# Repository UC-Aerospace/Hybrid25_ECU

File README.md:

# Hybrid Engine Control Unit

This repo contains the hardware and firmware for the 2025 Hybrid Rocket Engine FYP test stand electronics.

The hardware consists of three seperate modules, the central ECU alongside a servo and ADC peripheral. Central to peripheral
communication uses CAN-FD and is designed to be modular, while communications to a remote interface unit is done over RS422.
For more information on the RIU it can be found [here](https://github.com/UC-Aerospace/Hybrid25_RIU).

## Hardware

First thing to note, make sure you read the [issue!](https://github.com/UC-Aerospace/Hybrid25_ECU/issues/1).

There are issues with these designs, keep them in mind for any future development.

### MCU

The hardware of all these boards has been based on the STM32G0 MCU as a platform. The selection process for this was pretty
much based on wanting to use a STM32 for experience and the G0 in particular has two CAN-FD modems and was quite affordable.
This was a mistake, although it ended up working out okay. The STM32G0 critically lacks a SDIO peripheral which is a much
faster and more robust way of interacting with a SD card than SPI, as well as lacking QSPI and only having one SPI bus,
which meant we couldn't implement external flash memory for logging to. Given the issues with SD cards on an actual launch
vechicle that has been experienced I would have the following reccomendations:

* If you make new hardware switch MCU. Still use a ST product but pivot to something with SDIO and QSPI. Look into the F4, F7, H4 and H7 lines.
* Then implement a system where logging happens to flash during a test/launch, and then copies to SD afterwards. This means transfer to a PC
is still easy, you still get the bulk storage of SD but don't rely on it during high vibration periods.
* Don't go for a dual core. The cost increase dosn't justify the advantage and the complexity is significant.
* On cost the total sum of all the electronics this year was large enough not to worry about penny pinching on the MCU you buy maybe 5 of. $8 to $15
is inconsequential and well worth it if it saves you time.

Otherwise though the G0 has served it's purpose well this year. Honestly I have no idea how close we are cutting it with processing time overhead,
the MCU is plenty fast but a lot of the external I/O is quite slow (comms, sensors, SD card). Buffering is the name of the game in cases like that,
and trying to pass as much off to hardware peripherals as possible. Future teams could investigate a switch back to FreeRTOS for more flexibility around
scheduling, this will save some headaches and add a bunch more.

### Layout

Theres a bit of an explaination for the actual hardware design ethos to get you started in the Central ECU board directory. Otherwise between the
boards the main thing to talk about is connectors, comms and power.

The connectors we used on the peripheral boards were a compromise. JST's should never really be used where they might see forces on the wires,
but they are also cheap and the budget was getting out of hand. We mitigated this when testing by externally strain relieving all wires connecting
to both peripheral boards. Also when thinking about connectors try to keep in mind that if something can be plugged into the wrong place, it will
be plugged into the wrong place. Try to keep connectors dissimilar where you can, at least where damage would occur if they went the other way.

Comms is over CAN-FD for the peripheral to central communication and RS422 for central to RIU communication. The descision for this came because
CAN sounded cool to play with and RS422 seemed like the easiest way to get comms upto a couple hundred meters away. Both of these descisions played
out pretty well, with software headaches for both but nothing too serious. The CAN just uses premade serial DB9 cables, as these are cheap and easy
to get hold of. DB9 connectors are really solid and lock well, plus are rated to about 3A per pin. For the link to the RIU we just used generic CAT5
cable, two of the pairs are used for RS422 with another used for the ESTOP signal lines. The plastic connectors on either end are a weakspot, it would
have been nice to use something like etherCON connectors but again, expensive.

Power is something that got changed up a few times. We use lipo batteries as the power source, the ECU has two and theres an extra for the servos. The
ECU has a 2S for general functions, which is also passed to the peripherals which they use. The servo board uses this for the 2 7.4V servos remaining also.
The other battery in the ECU, the 6S, is used for the solenoids and ignitors. This is the power that the ESTOP is inline with, cutting that will abort the
test due to the normally closed solenoid. Finally as we had to add 24V servos there is a seperate 6S battery dedicated to them during the test. This is suboptimal
as we have no insight into the level of it remotely during a test and the standby draw is quite high. If done again just plug this directly into the servo board
and move all servos to 24V. 

## Software

I have yet to find a way to make code sound interesting, and I don't think I'm going to manage it here either. I guess the main thing to point out is there is
a lot of code. Certainly more than I expected going into this, and it took significantly longer than I expected as well. Main word of advice with the software,
it is very easy to get yourself stuck in a trap of rushing rubbish code out.

There was an extended period this year when we were perpetually two weeks away from testing, and it probably shows in the code. In the end the hold up was with
another system, but the code was still blasted out dangerously fast regardless. Give yourself time in the beginning and temper the goals, its easy to add more
later but hard to strip them away with testing looming.

For some more specifics on the actual code I'll leave a quick README for the specifics under each boards code. Heres a quick rant from the EOY report though.

*All code and hardware design has been done in a single git repository. This was poor practice, in future break the code up into separate repositories, 
the only reason we could make a single repository work is because only one person was working on it. One of the main motivators for doing it this way was to enable
code reuse between the boards, for example the CAN module is common between all three and uses a symbolic linked folder. In future it would be worth investigating
using git submodules for the same thing. VS Code was used as the IDE for the ECU and peripherals, while STM32CubeIDE was used for the RIU. It is **strongly** recommended
that future teams do not use CubeIDE, while IDE’s are a preference eclipse is objectively terrible. The ST support for VS Code is good enough now that after installing
the extensions and CubeMX the development experience is much better.*

*The general layout for each board is given below:*

### Finite State Machine Diagrams

#### Central ECU

#### Servo Module

### ADC Module

The ADC module has no inherent state machine, it just reads sensors and sends these.

## Operational

### Safety

Safety has been one of the major concerns with this project. To try and mitigate some of those concerns the main solenoid
is normally closed, such that within 350 milliseconds of cutting the power it fully shuts. The ignitors, being potentially
explosive, were also identified as high risk. Therefore, both these items are on a seperate circuit. Two air gaps exist
in this loop, one E-Stop positioned inline and outside the test container, another at the RIU and connected through a relay
to limit current loss.

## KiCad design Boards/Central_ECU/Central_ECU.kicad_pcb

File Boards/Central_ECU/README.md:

# Central ECU

The central ECU is pretty simple and carries out a couple of tasks. Firstly is comms which is easy to see with CAN on the left and RS422 on the right
of the schematic. The SD card occupies the top right, with pull up resistors on the main data lines. The top right has a display over I2C and a
pressure and temp sensor. On the status LED front the other boards had two controlled from GPIOs while the central ECU only has one. Two is much
better as you can have a status and error LED, don't discount just how useful a few LEDs are. And finally the interesting bit is probably the spicy stuff.

This is for the control of the single solenoid and two ignitor channels. The layout is very similar for both, except the ignitors have continuity detection
as well. First off theres a connector populated to allow for an external regulator if the voltage requirements of the solenoid changes. This occured as we
made this board before selecting a solenoid. A comparator then is used on the input so we know when the RIU and external ESTOP are released.

For the actual switching there is both a high and low side switch. The high side switch is common to both ignitors and solenoid, and comes in the form of a
EFuse. Theres some big advantages to doing it this way, for one it limits the current spike that occurs when switching the outputs, and also will protect the
circuit in the case of a shorted output. A GPIO toggles this, allowing for a hardware "Arm" controlled by software. A 2K resistor bypasses the highside switch,
this allows for continuity detection. Nominally no current will flow through this as the low side switches will be off, but even if one of the low side switches
is on the current is limited to 15mA, too low to ignite one of the ignitors or open the solenoid. This dual switching design also provides some reassurance in
the case of a FET failing as they usually fail shorted, allowing the test to be terminated by the ECU regardless of a single failure.

The connectors are another area that might be worth mentioning briefly. It is generally good practice to make sure that things physically can't be plugged in
wrong, because someone will definitly plug that 6S battery into your 2S circuit otherwise. You can see I have designed it such that the 2S and 6S input shares
the same sort of connector, but has the voltage on a different pin so if they get plugged in the wrong way around it dosn't matter. Doing this everywhere will
get impractical, for instance the on and arm switches are the same, but think about the critical places to do this and make sure you do. Either use a different
connector type or different number of pins to switch it up.

Final rant for this section, be careful with your linear voltage regulators. They will have a rated current but thats never really achievable due to thermals.
Make sure you actually do some thermal calculations and stitch the regulators through into the planes underneath with plenty of vias. And chaining the regulators
is another approach, I needed 5V but had very little 5V draw, so by inputting 5V to the 3.3V regulator you effectivly split the heat across both regulators.

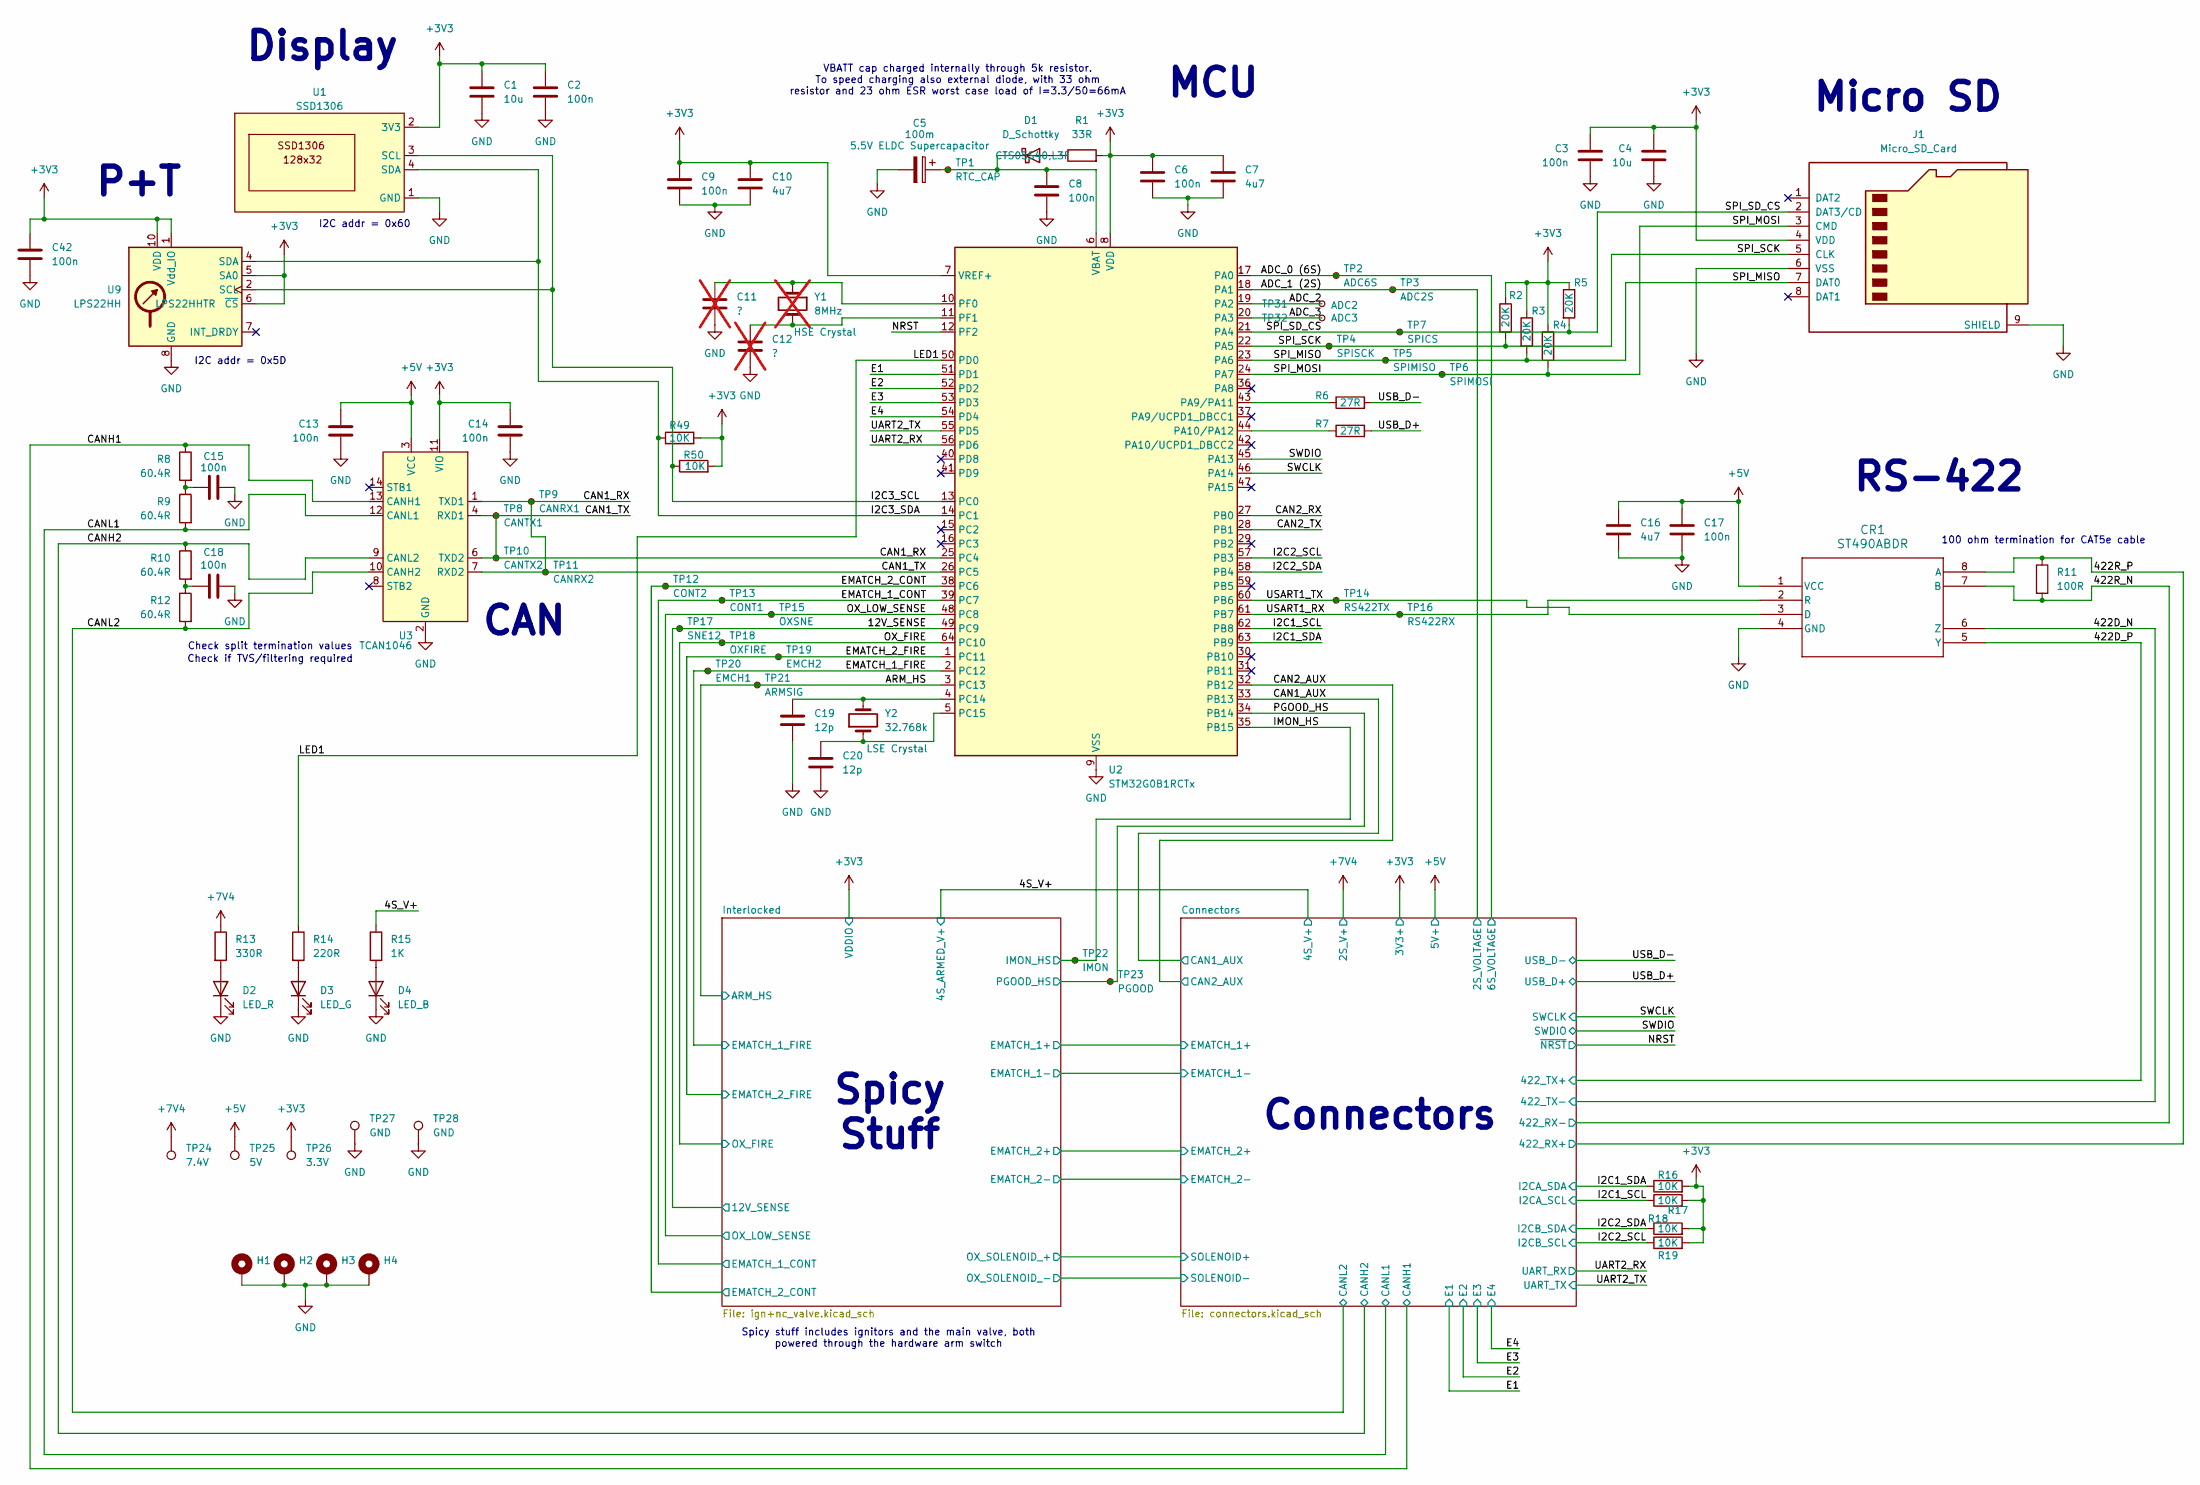
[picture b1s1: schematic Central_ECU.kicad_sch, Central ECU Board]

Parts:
C1, C4: 10u; C_0603_1608Metric
C2, C3, C13, C14, C15, C17, C18, C42: 100n; C_0603_1608Metric
C5: 100m; CP_Radial_D14.0mm_P5.00mm; MPN RSCBN1045R5G07014T
C6, C8, C9: 100n; C_0402_1005Metric
C7, C10, C16: 4u7; C_0603_1608Metric
C11, C12: ?; C_0402_1005Metric; not fitted
C19, C20: 12p; C_0402_1005Metric
CR1: ST490ABDR; SO-8_3.9x4.9mm_P1.27mm; MPN ST490ABDR
D1: D_Schottky; D_SOD-882; MPN CTS05S40,L3F
D2: LED_R; LED_1206_3216Metric; MPN LTST-C150KRKT
D3: LED_G; LED_1206_3216Metric; MPN LTST-C150KGKT
D4: LED_B; LED_1206_3216Metric; MPN LTST-C150TBKT
H1, H2, H3, H4: MountingHole_3.2mm_M3_DIN965_Pad_TopOnly
J1: Micro_SD_Card; microSD_HC_Molex_47219-2001; MPN 0472192001
R1: 33R; R_0603_1608Metric
R2, R3, R4, R5: 20K; R_0603_1608Metric
R6, R7: 27R; R_0603_1608Metric
R8, R9, R10, R12: 60.4R; R_0603_1608Metric
R11: 100R; R_0603_1608Metric
R13: 330R; R_0603_1608Metric
R14: 220R; R_0603_1608Metric
R15: 1K; R_0603_1608Metric
R16, R17, R18, R19, R49, R50: 10K; R_0603_1608Metric
TP1: RTC_CAP; TestPoint_Pad_1.5x1.5mm
TP2: ADC6S; TestPoint_Pad_1.5x1.5mm
TP3: ADC2S; TestPoint_Pad_1.5x1.5mm
TP4: SPISCK; TestPoint_Pad_1.5x1.5mm
TP5: SPIMISO; TestPoint_Pad_1.5x1.5mm
TP6: SPIMOSI; TestPoint_Pad_1.5x1.5mm
TP7: SPICS; TestPoint_Pad_1.5x1.5mm
TP8: CANTX1; TestPoint_Pad_1.5x1.5mm
TP9: CANRX1; TestPoint_Pad_1.5x1.5mm
TP10: CANTX2; TestPoint_Pad_1.5x1.5mm
TP11: CANRX2; TestPoint_Pad_1.5x1.5mm
TP12: CONT2; TestPoint_Pad_1.5x1.5mm
TP13: CONT1; TestPoint_Pad_1.5x1.5mm
TP14: RS422TX; TestPoint_Pad_1.5x1.5mm
TP15: OXSNE; TestPoint_Pad_1.5x1.5mm
TP16: RS422RX; TestPoint_Pad_1.5x1.5mm
TP17: SNE12; TestPoint_Pad_1.5x1.5mm
TP18: OXFIRE; TestPoint_Pad_1.5x1.5mm
TP19: EMCH2; TestPoint_Pad_1.5x1.5mm
TP20: EMCH1; TestPoint_Pad_1.5x1.5mm
TP21: ARMSIG; TestPoint_Pad_1.5x1.5mm
TP22: IMON; TestPoint_Pad_1.5x1.5mm
TP23: PGOOD; TestPoint_Pad_1.5x1.5mm
TP24: 7.4V; TestPoint_Pad_1.5x1.5mm
TP25: 5V; TestPoint_Pad_1.5x1.5mm
TP26: 3.3V; TestPoint_Pad_1.5x1.5mm
TP27, TP28: GND; TestPoint_Bridge_Pitch2.54mm_Drill1.3mm
TP31: ADC2; TestPoint_Pad_1.5x1.5mm
TP32: ADC3; TestPoint_Pad_1.5x1.5mm
U1: SSD1306; SSD1306-0.91-OLED-4pin-128x32; MPN N/A
U2: STM32G0B1RCTx; LQFP-64_10x10mm_P0.5mm; MPN STM32G0B1RCT6
U3: TCAN1046; SOT23_DYY_TEX; MPN TCAN1046AVDYYRQ1
U9: LPS22HH; ST_HLGA-10_2x2mm_P0.5mm_LayoutBorder3x2y; MPN LPS22HHTR
Y1: 8MHz; Crystal_SMD_Abracon_ABM8G-4Pin_3.2x2.5mm; not fitted
Y2: 32.768k; Crystal_SMD_2012-2Pin_2.0x1.2mm; MPN ABS06-32.768KHZ-1-T

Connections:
+3V3: C1.1, C2.1, C3.1, C4.1, C6.1, C7.1, C9.1, C10.1, C14.1, C42.1, J1.4 (VDD), R1.2, R2.1, R3.1, R4.1, R5.1, R16.2, R17.2, R18.2, R19.2, R49.2, R50.2, TP26.1, U1.2 (3V3), U2.7 (VREF+), U2.8 (VDD), U3.11 (VIO), U9.1 (Vdd_IO), U9.5 (SA0), U9.6 (~CS), U9.10 (VDD); also elsewhere on the board
+5V: C13.1, C16.1, C17.1, CR1.1 (VCC), TP25.1, U3.3 (VCC); also elsewhere on the board
+7V4: R13.1, TP24.1; also elsewhere on the board
/4S_V+: R15.1; also elsewhere on the board
/12V_SENSE: TP17.1, U2.49 (PC9); also elsewhere on the board
/422D_N: CR1.6 (Z); also elsewhere on the board
/422D_P: CR1.5 (Y); also elsewhere on the board
/422R_N: CR1.7 (B), R11.2; also elsewhere on the board
/422R_P: CR1.8 (A), R11.1; also elsewhere on the board
/ADC_0 (6S): TP2.1, U2.17 (PA0); also elsewhere on the board
/ADC_1 (2S): TP3.1, U2.18 (PA1); also elsewhere on the board
/ADC_2: TP31.1, U2.19 (PA2)
/ADC_3: TP32.1, U2.20 (PA3)
/ARM_HS: TP21.1, U2.3 (PC13); also elsewhere on the board
/CAN1_AUX: U2.33 (PB13); also elsewhere on the board
/CAN1_RX: TP8.1, TP9.1, TP10.1, TP11.1, U2.25 (PC4), U2.26 (PC5), U3.1 (TXD1), U3.4 (RXD1), U3.6 (TXD2), U3.7 (RXD2)
/CAN2_AUX: U2.32 (PB12); also elsewhere on the board
/CAN2_RX: U2.27 (PB0)
/CAN2_TX: U2.28 (PB1)
/CANH1: R8.1, U3.13 (CANH1); also elsewhere on the board
/CANH2: R10.1, U3.9 (CANL2); also elsewhere on the board
/CANL1: R9.2, U3.12 (CANL1); also elsewhere on the board
/CANL2: R12.2, U3.10 (CANH2); also elsewhere on the board
/E1: U2.51 (PD1); also elsewhere on the board
/E2: U2.52 (PD2); also elsewhere on the board
/E3: U2.53 (PD3); also elsewhere on the board
/E4: U2.54 (PD4); also elsewhere on the board
/EMATCH_1_CONT: TP13.1, U2.39 (PC7); also elsewhere on the board
/EMATCH_1_FIRE: TP20.1, U2.2 (PC12); also elsewhere on the board
/EMATCH_2_CONT: TP12.1, U2.38 (PC6); also elsewhere on the board
/EMATCH_2_FIRE: TP19.1, U2.1 (PC11); also elsewhere on the board
/I2C1_SCL: R17.1, U2.62 (PB8); also elsewhere on the board
/I2C1_SDA: R16.1, U2.63 (PB9); also elsewhere on the board
/I2C2_SCL: R19.1, U2.57 (PB3); also elsewhere on the board
/I2C2_SDA: R18.1, U2.58 (PB4); also elsewhere on the board
/I2C3_SCL: R50.1, U1.3 (SCL), U2.13 (PC0), U9.2 (SCL)
/I2C3_SDA: R49.1, U1.4 (SDA), U2.14 (PC1), U9.4 (SDA)
/IMON_HS: TP22.1, U2.35 (PB15); also elsewhere on the board
/LED1: R14.1, U2.50 (PD0)
/NRST: U2.12 (PF2); also elsewhere on the board
/OX_FIRE: TP18.1, U2.64 (PC10); also elsewhere on the board
/OX_LOW_SENSE: TP15.1, U2.48 (PC8); also elsewhere on the board
/PGOOD_HS: TP23.1, U2.34 (PB14); also elsewhere on the board
/SPI_MISO: J1.7 (DAT0), R3.2, TP5.1, U2.23 (PA6)
/SPI_MOSI: J1.3 (CMD), R4.2, TP6.1, U2.24 (PA7)
/SPI_SCK: J1.5 (CLK), R2.2, TP4.1, U2.22 (PA5)
/SPI_SD_CS: J1.2 (DAT3/CD), R5.2, TP7.1, U2.21 (PA4)
/SWCLK: U2.46 (PA14); also elsewhere on the board
/SWDIO: U2.45 (PA13); also elsewhere on the board
/UART2_RX: U2.56 (PD6); also elsewhere on the board
/UART2_TX: U2.55 (PD5); also elsewhere on the board
/USART1_RX: CR1.2 (R), TP16.1, U2.61 (PB7)
/USART1_TX: CR1.3 (D), TP14.1, U2.60 (PB6)
/USB_D+: R7.2; also elsewhere on the board
/USB_D-: R6.2; also elsewhere on the board
GND: C1.2, C2.2, C3.2, C4.2, C5.2, C6.2, C7.2, C8.2, C9.2, C10.2, C11.2, C12.2, C13.2, C14.2, C15.1, C16.2, C17.2, C18.1, C19.2, C20.2, C42.2, CR1.4 (GND), D2.1 (K), D3.1 (K), D4.1 (K), H1.1, H2.1, H3.1, H4.1, J1.6 (VSS), J1.9 (SHIELD), TP27.1, TP28.1, U1.1 (GND), U2.9 (VSS), U3.2 (GND), U3.5 (GND), U9.3 (GND), U9.8 (GND), U9.9 (GND); also elsewhere on the board
unnamed: C15.2, R8.2, R9.1
unnamed: C18.2, R10.2, R12.1
unnamed: D1.2 (A), R1.1
unnamed: C5.1, C8.1, D1.1 (K), TP1.1, U2.6 (VBAT)
unnamed: D2.2 (A), R13.2
unnamed: D3.2 (A), R14.2
unnamed: D4.2 (A), R15.2
unnamed: R6.1, U2.43 (PA9/PA11)
unnamed: R7.1, U2.44 (PA10/PA12)
unnamed: C19.1, U2.4 (PC14), Y2.2
unnamed: C20.1, U2.5 (PC15), Y2.1
unnamed: C11.1, U2.10 (PF0), Y1.1
unnamed: C12.1, U2.11 (PF1), Y1.3 (2)

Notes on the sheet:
VBATT cap charged internally through 5k resistor. To speed charging also external diode, with 33 ohm resistor and 23 ohm ESR worst case load of I=3.3/50=66mA
Display
Connectors
RS-422
I2C addr = 0x60
Spicy Stuff
100 ohm termination for CAT5e cable
I2C addr = 0x5D
CAN
P+T
Check if TVS/filtering required
Micro SD
Check split termination values
Spicy stuff includes ignitors and the main valve, both powered through the hardware arm switch
MCU

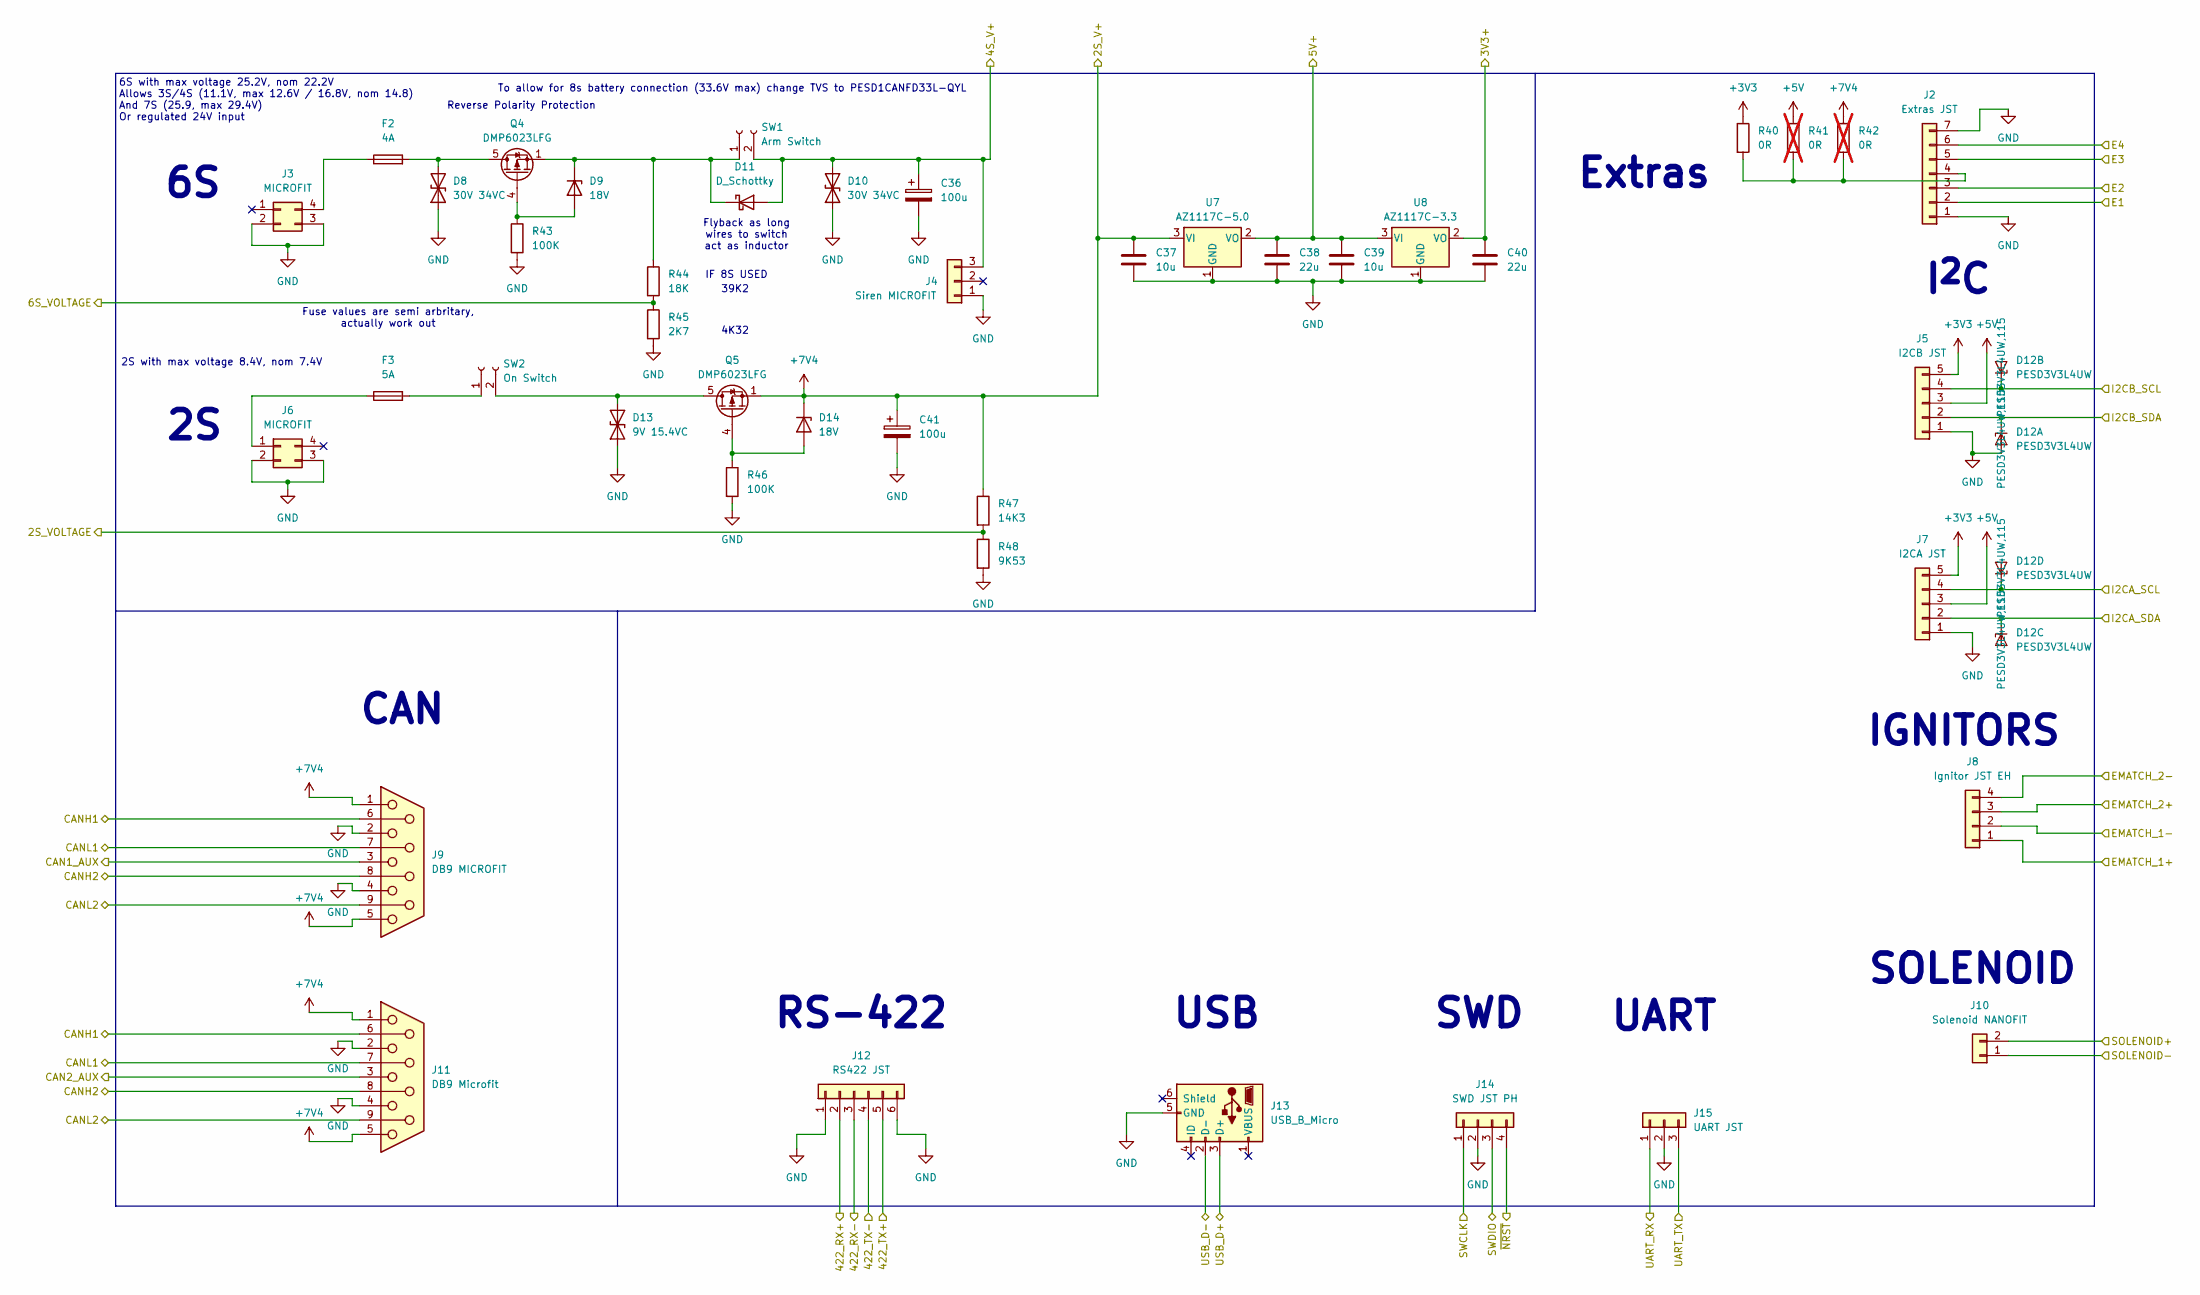
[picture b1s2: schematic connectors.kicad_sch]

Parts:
C36, C41: 100u; CP_Elec_8x10.5; MPN A768KS107M1HLAE030
C37, C39: 10u; C_0603_1608Metric
C38, C40: 22u; C_1206_3216Metric
D8, D10: 30V 34VC; D_SOD-882; MPN PESD1CANFD30L-QYL
D9, D14: 18V; D_SOD-323F; MPN MM3Z18VB
D11: D_Schottky; D_SOD-882; MPN CTS05S40,L3F
D12: PESD3V3L4UW; SOT-665; MPN PESD3V3L4UW,115
D13: 9V 15.4VC; D_SOD-123F; MPN SMF9.0CA
F2: 4A; Fuse_1206_3216Metric
F3: 5A; Fuse_1206_3216Metric
J2: Extras JST; JST_PH_B7B-PH-K_1x07_P2.00mm_Vertical; MPN B7B-PH-K-S
J3, J6: MICROFIT; Molex_Micro-Fit_3.0_43045-0412_2x02_P3.00mm_Vertical; MPN 0430450412
J4: Siren MICROFIT; Molex_Micro-Fit_3.0_43650-0315_1x03_P3.00mm_Vertical; MPN 436500315
J5: I2CB JST; JST_PH_B5B-PH-K_1x05_P2.00mm_Vertical; MPN B6B-PH-K-S
J7: I2CA JST; JST_PH_B5B-PH-K_1x05_P2.00mm_Vertical; MPN B5B-PH-K-S
J8: Ignitor JST EH; JST_EH_B4B-EH-A_1x04_P2.50mm_Vertical; MPN B4B-EH-A
J9: DB9 MICROFIT; Molex_Micro-Fit_3.0_43045-1012_2x05_P3.00mm_Vertical; MPN 0430451027
J10: Solenoid NANOFIT; Molex_Nano-Fit_105309-xx02_1x02_P2.50mm_Vertical; MPN 1053091102
J11: DB9 Microfit; Molex_Micro-Fit_3.0_43045-1012_2x05_P3.00mm_Vertical; MPN 0430451027
J12: RS422 JST; JST_PH_B6B-PH-K_1x06_P2.00mm_Vertical; MPN B6B-PH-K-S
J13: USB_B_Micro; USB_Micro-B_Amphenol_10118193-0001LF_Horizontal; MPN 10118193-0001LF
J14: SWD JST PH; JST_PH_B4B-PH-K_1x04_P2.00mm_Vertical; MPN B4B-PH-K-S
J15: UART JST; JST_PH_B3B-PH-K_1x03_P2.00mm_Vertical; MPN B3B-PH-K-S
Q4, Q5: DMP6023LFG; Diodes_PowerDI3333-8; MPN DMP6023LFG-7
R40: 0R; R_0603_1608Metric
R41, R42: 0R; R_0603_1608Metric; not fitted
R43, R46: 100K; R_0603_1608Metric
R44: 18K; R_0603_1608Metric
R45: 2K7; R_0603_1608Metric
R47: 14K3; R_0603_1608Metric
R48: 9K53; R_0603_1608Metric
SW1: Arm Switch; Molex_Micro-Fit_3.0_43650-0215_1x02_P3.00mm_Vertical; MPN 436500228
SW2: On Switch; Molex_Micro-Fit_3.0_43650-0215_1x02_P3.00mm_Vertical; MPN 436500228
U7: AZ1117C-5.0; SOT-223-3_TabPin2; MPN AZ1117CH-5.0TRG1
U8: AZ1117C-3.3; SOT-223-3_TabPin2; MPN AZ1117CH-3.3TRG1

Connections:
+3V3: C40.1, J5.5, J7.5, R40.1, U8.2 (VO); also elsewhere on the board
+5V: C38.1, C39.1, J5.3, J7.3, R41.1, U7.2 (VO), U8.3 (VI); also elsewhere on the board
+7V4: C37.1, C41.1, D14.1 (K), J9.1, J9.5, J11.1, J11.5, Q5.1 (S), Q5.2 (S), Q5.3 (S), R42.1, R47.1, U7.3 (VI); also elsewhere on the board
/4S_V+: C36.1, D10.2 (A2), D11.2 (A), J4.3, SW1.2; also elsewhere on the board
/422D_N: J12.4; also elsewhere on the board
/422D_P: J12.5; also elsewhere on the board
/422R_N: J12.3; also elsewhere on the board
/422R_P: J12.2; also elsewhere on the board
/ADC_0 (6S): R44.2, R45.1; also elsewhere on the board
/ADC_1 (2S): R47.2, R48.1; also elsewhere on the board
/CAN1_AUX: J9.3; also elsewhere on the board
/CAN2_AUX: J11.3; also elsewhere on the board
/CANH1: J9.6, J11.6; also elsewhere on the board
/CANH2: J9.8, J11.8; also elsewhere on the board
/CANL1: J9.7, J11.7; also elsewhere on the board
/CANL2: J9.9, J11.9; also elsewhere on the board
/Connectors/EMATCH_1+: J8.1, J8.3; also elsewhere on the board
/Connectors/EMATCH_1-: J8.2; also elsewhere on the board
/Connectors/EMATCH_2-: J8.4; also elsewhere on the board
/Connectors/SOLENOID+: J10.2; also elsewhere on the board
/Connectors/SOLENOID-: J10.1; also elsewhere on the board
/E1: J2.2; also elsewhere on the board
/E2: J2.3; also elsewhere on the board
/E3: J2.5; also elsewhere on the board
/E4: J2.6; also elsewhere on the board
/I2C1_SCL: D12.5 (K4), J7.4; also elsewhere on the board
/I2C1_SDA: D12.4 (K3), J7.2; also elsewhere on the board
/I2C2_SCL: D12.3 (K2), J5.4; also elsewhere on the board
/I2C2_SDA: D12.1 (K1), J5.2; also elsewhere on the board
/NRST: J14.4; also elsewhere on the board
/SWCLK: J14.1; also elsewhere on the board
/SWDIO: J14.3; also elsewhere on the board
/UART2_RX: J15.1; also elsewhere on the board
/UART2_TX: J15.3; also elsewhere on the board
/USB_D+: J13.3 (D+); also elsewhere on the board
/USB_D-: J13.2 (D-); also elsewhere on the board
GND: C36.2, C37.2, C38.2, C39.2, C40.2, C41.2, D8.1 (A1), D10.1 (A1), D12.2 (A), D13.1 (A1), J2.1, J2.7, J3.2, J3.3, J4.1, J5.1, J6.2, J6.3, J7.1, J9.2, J9.4, J11.2, J11.4, J12.1, J12.6, J13.5 (GND), J14.2, J15.2, R43.2, R45.2, R46.2, R48.2, U7.1 (GND), U8.1 (GND); also elsewhere on the board
unnamed: D8.2 (A2), F2.2, Q4.5 (D)
unnamed: D9.2 (A), Q4.4 (G), R43.1
unnamed: D9.1 (K), D11.1 (K), Q4.1 (S), Q4.2 (S), Q4.3 (S), R44.1, SW1.1
unnamed: D13.2 (A2), Q5.5 (D), SW2.2
unnamed: D14.2 (A), Q5.4 (G), R46.1
unnamed: J2.4, R40.2, R41.2, R42.2
unnamed: F2.1, J3.4
unnamed: F3.1, J6.1
unnamed: F3.2, SW2.1

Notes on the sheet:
CAN
To allow for 8s battery connection (33.6V max) change TVS to PESD1CANFD33L-QYL
USB
Flyback as long wires to switch act as inductor
SOLENOID
RS-422
IGNITORS
Extras
2S with max voltage 8.4V, nom 7.4V
Fuse values are semi arbritary, actually work out
4K32
6S with max voltage 25.2V, nom 22.2V Allows 3S/4S (11.1V, max 12.6V / 16.8V, nom 14.8) And 7S (25.9, max 29.4V) Or regulated 24V input
IF 8S USED
39K2
Reverse Polarity Protection
UART
SWD
I^{2}C

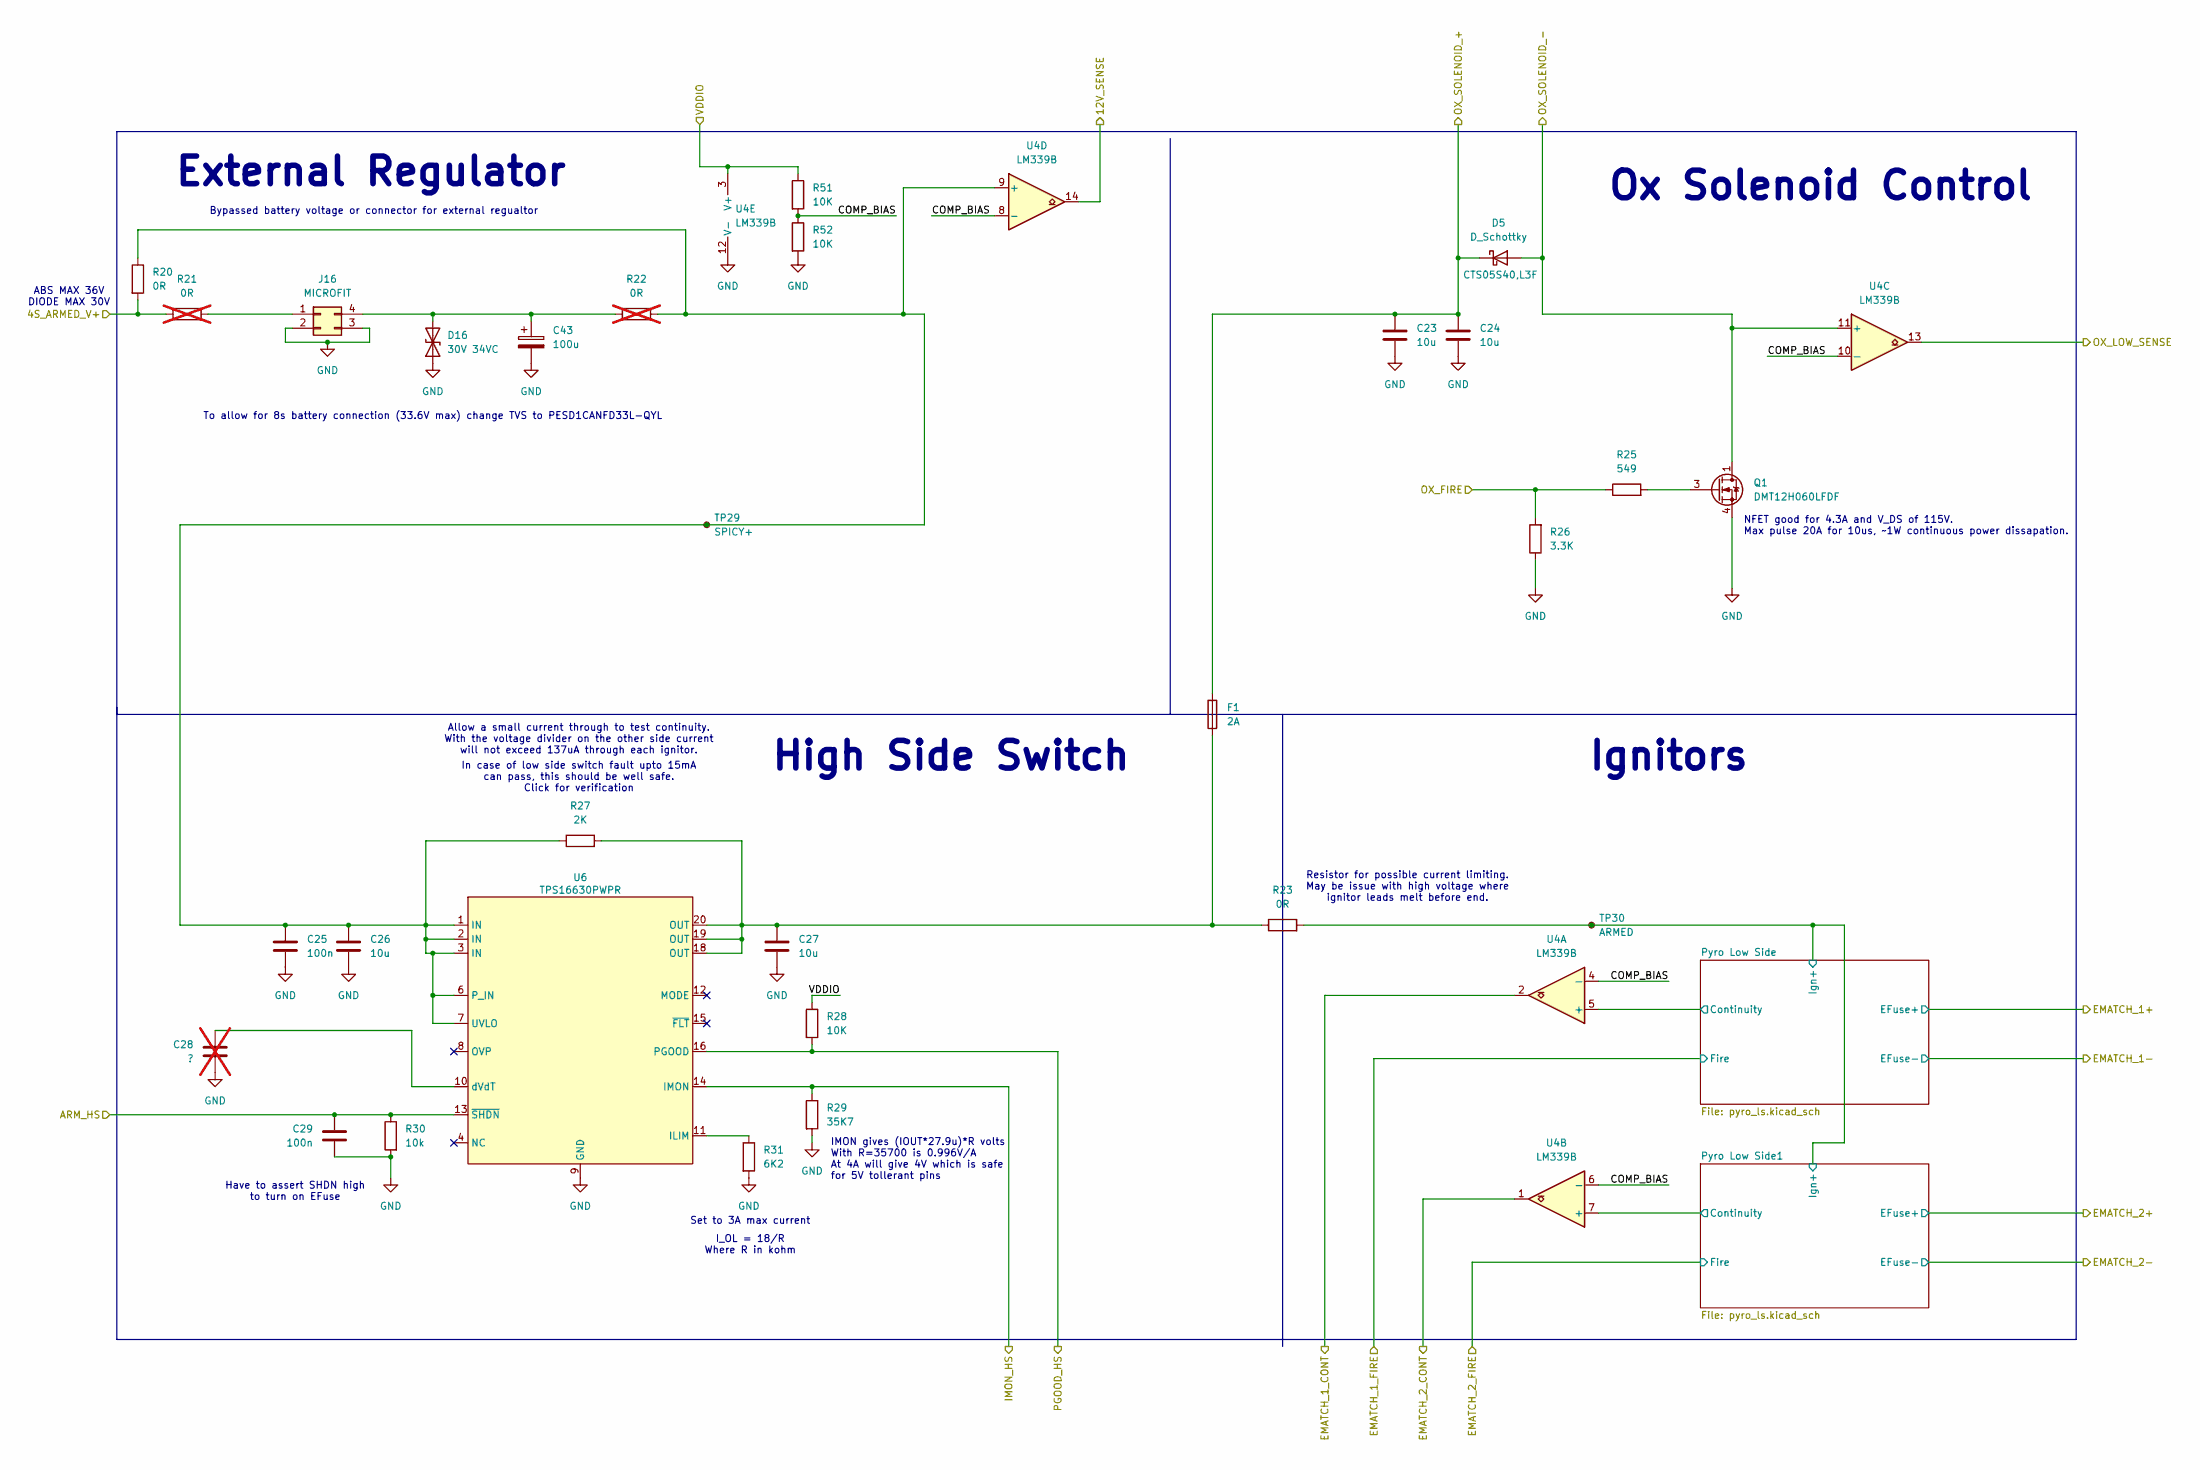
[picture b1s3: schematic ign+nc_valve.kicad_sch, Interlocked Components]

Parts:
C23, C24, C26, C27: 10u; C_1206_3216Metric
C25, C29: 100n; C_0603_1608Metric
C28: ?; C_0603_1608Metric; not fitted
C43: 100u; CP_Elec_8x10.5; MPN A768KS107M1HLAE030
D5: D_Schottky; D_SOD-882; MPN CTS05S40,L3F
D16: 30V 34VC; D_SOD-882; MPN PESD1CANFD30L-QYL
F1: 2A; Fuse_1206_3216Metric
J16: MICROFIT; Molex_Micro-Fit_3.0_43045-0412_2x02_P3.00mm_Vertical; MPN 0430450412
Q1: DMT12H060LFDF; Diodes_UDFN2020-6_Type-F; MPN DMT12H060LFDF-7
R20, R23: 0R; R_1206_3216Metric
R21, R22: 0R; R_1206_3216Metric; not fitted
R25: 549; R_0603_1608Metric
R26: 3.3K; R_0603_1608Metric
R27: 2K; R_0603_1608Metric
R28, R51, R52: 10K; R_0603_1608Metric
R29: 35K7; R_0603_1608Metric
R30: 10k; R_0603_1608Metric
R31: 6K2; R_0603_1608Metric
TP29: SPICY+; TestPoint_Pad_1.5x1.5mm
TP30: ARMED; TestPoint_Pad_1.5x1.5mm
U4: LM339B; TSSOP-14_4.4x5mm_P0.65mm; MPN LM339BIPWR
U6: TPS16630PWPR; HTSSOP-20-1EP_4.4x6.5mm_P0.65mm_EP3.4x6.5mm_Mask2.96x2.96mm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; MPN TPS16630PWPR

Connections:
+3V3: R28.1, R51.1, U4.3 (V+); also elsewhere on the board
/4S_V+: R20.2, R21.1; also elsewhere on the board
/12V_SENSE: U4.14; also elsewhere on the board
/ARM_HS: C29.1, R30.1, U6.13 (~SHDN); also elsewhere on the board
/Connectors/EMATCH_1+: R23.2, TP30.1; also elsewhere on the board
/Connectors/SOLENOID+: C23.1, C24.1, D5.1 (K), F1.2; also elsewhere on the board
/Connectors/SOLENOID-: D5.2 (A), Q1.1, Q1.2 (D), Q1.5 (D), Q1.6 (D), Q1.7 (D), U4.11 (+); also elsewhere on the board
/EMATCH_1_CONT: U4.2; also elsewhere on the board
/EMATCH_2_CONT: U4.1; also elsewhere on the board
/IMON_HS: R29.1, U6.14 (IMON); also elsewhere on the board
/Interlocked/COMP_BIAS: R51.2, R52.1, U4.4 (-), U4.6 (-), U4.8 (-), U4.10 (-)
/Interlocked/Pyro Low Side1/Continuity: U4.7 (+); also elsewhere on the board
/Interlocked/Pyro Low Side/Continuity: U4.5 (+); also elsewhere on the board
/OX_FIRE: R25.1, R26.2; also elsewhere on the board
/OX_LOW_SENSE: U4.13; also elsewhere on the board
/PGOOD_HS: R28.2, U6.16 (PGOOD); also elsewhere on the board
GND: C23.2, C24.2, C25.2, C26.2, C27.2, C28.2, C29.2, C43.2, D16.1 (A1), J16.2, J16.3, Q1.4, Q1.8 (S), R26.1, R29.2, R30.2, R31.2, R52.2, U4.12 (V-), U6.9 (GND), U6.21 (GND); also elsewhere on the board
unnamed: C27.1, F1.1, R23.1, R27.2, U6.18 (OUT), U6.19 (OUT), U6.20 (OUT)
unnamed: C43.1, D16.2 (A2), J16.4, R22.1
unnamed: J16.1, R21.2
unnamed: Q1.3, R25.2
unnamed: C25.1, C26.1, R20.1, R22.2, R27.1, TP29.1, U4.9 (+), U6.1 (IN), U6.2 (IN), U6.3 (IN), U6.6 (P_IN), U6.7 (UVLO)
unnamed: R31.1, U6.11 (ILIM)
unnamed: C28.1, U6.10 (dVdT)

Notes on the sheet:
ABS MAX 36V DIODE MAX 30V
Have to assert SHDN high to turn on EFuse
External Regulator
NFET good for 4.3A and V_DS of 115V. Max pulse 20A for 10us, ~1W continuous power dissapation.
Set to 3A max current
To allow for 8s battery connection (33.6V max) change TVS to PESD1CANFD33L-QYL
Ox Solenoid Control
Ignitors
Bypassed battery voltage or connector for external regualtor
I_OL = 18/R Where R in kohm
Resistor for possible current limiting. May be issue with high voltage where ignitor leads melt before end.
In case of low side switch fault upto 15mA can pass, this should be well safe. Click for verification
Allow a small current through to test continuity. With the voltage divider on the other side current will not exceed 137uA through each ignitor.
IMON gives (IOUT*27.9u)*R volts With R=35700 is 0.996V/A At 4A will give 4V which is safe for 5V tollerant pins
High Side Switch
